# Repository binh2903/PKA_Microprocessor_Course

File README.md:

# PKA_Microprocessor_Course-
This repository contains the key submissions for the PKA Microprocessor Course, including classroom exercises, the mid-term report, and the final presentation.

Contents
Classroom Practice (1_THUC_HANH/)

This folder contains exercises and practical assignments completed during the course.

It includes hands-on work with microprocessors, programming tasks, and hardware-related experiments.

Mid-Term Report (2_Mid_Term_Report/)

A comprehensive report summarizing our progress and findings at the mid-point of the course.

It covers theoretical concepts, implementation details, and challenges encountered.

Final Presentation (3_Final_Presentation/)

The final presentation, showcasing our major project.

This includes an overview of the project's objectives, methodology, results, and conclusions.

This repository represents our team's collaborative efforts throughout the course, demonstrating both theoretical knowledge and practical application in microprocessor technology.

Note:
This README was generated with assistance from AI (ChatGPT) to ensure clarity and completeness.

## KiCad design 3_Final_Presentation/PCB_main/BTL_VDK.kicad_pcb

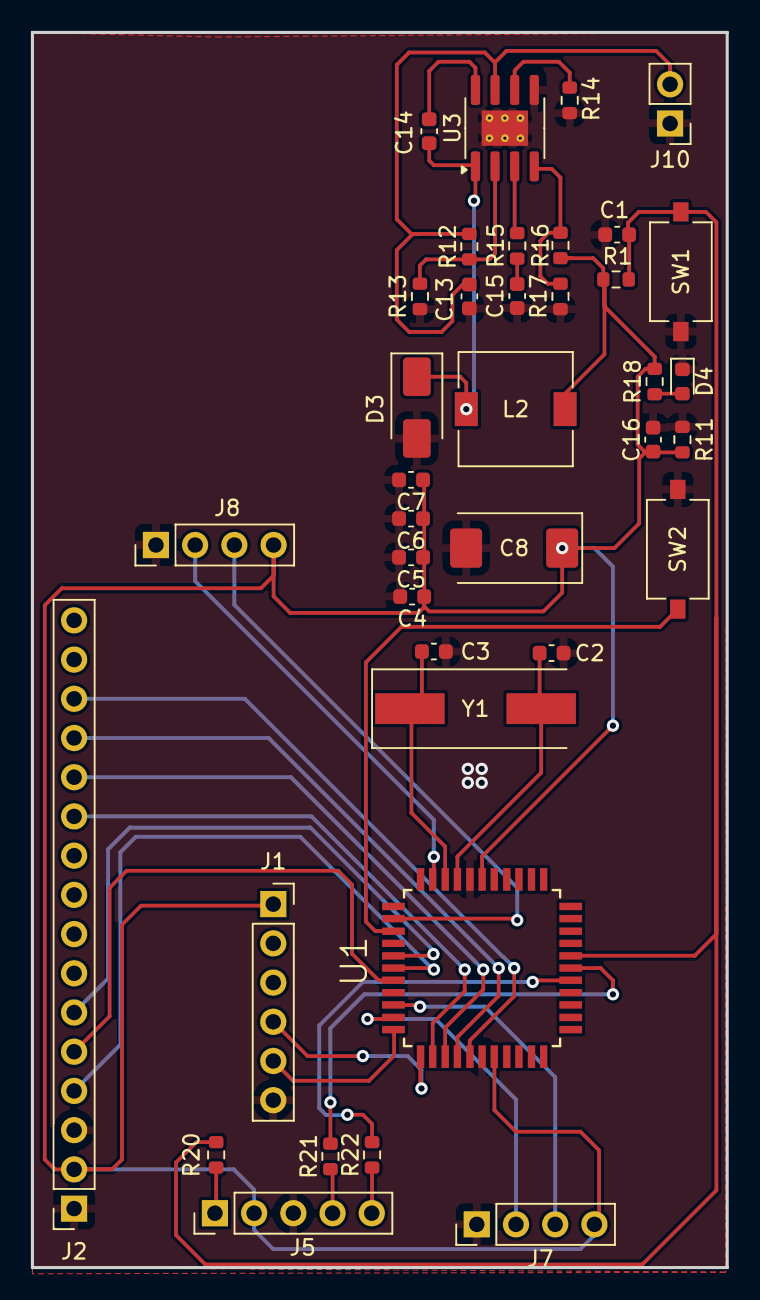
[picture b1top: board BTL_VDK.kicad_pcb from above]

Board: 2 copper layers, 45.0 x 80.0 mm, 38 parts (0 on the bottom side), 33 nets.

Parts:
C1, C5, C7: 10n; C_0603_1608Metric
C2, C3: 10p; C_0603_1608Metric
C4, C6, C13, C14: 100n; C_0603_1608Metric
C8: 47u; CP_EIA-7343-30_AVX-N
C15: 150p; C_0603_1608Metric
C16: 22u; C_0603_1608Metric
D3: SS34; D_SMA
D4: 5V; LED_0603_1608Metric
J1: Conn_01x06_Socket; PinSocket_1x06_P2.54mm_Vertical
J2: Conn_01x16_Socket; PinSocket_1x16_P2.54mm_Vertical
J5: ISP_CON; PinHeader_1x05_P2.54mm_Vertical
J7, J8: JST 2.54X4; PinHeader_1x04_P2.54mm_Vertical
J10: POWER; PinHeader_1x02_P2.54mm_Vertical
L2: 10uH; L_7.3x7.3_H3.5
R1, R11: 4.7K; R_0603_1608Metric
R12, R14, R15, R16, R17, R18: 10K; R_0603_1608Metric
R13: 10; R_0603_1608Metric
R20, R21, R22: 10R; R_0603_1608Metric
SW1: RST_BUT; SW_Tactile_SPST_NO_Straight_CK_PTS636Sx25SMTRLFS
SW2: RST_BUT_loadcell; SW_Tactile_SPST_NO_Straight_CK_PTS636Sx25SMTRLFS
U1: PIC16F887-I_PT; QFP80P1200X1200X120-44N
U3: MP1584EN-LF-P; SOIC-8-1EP_3.9x4.9mm_P1.27mm_EP2.29x3mm_ThermalVias
Y1: 20M; Crystal_SMD_HC49-SD

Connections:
12: C13.2, J10.2, R12.2, U3.7 (VIN)
+5V: C4.1, C5.1, C6.1, C7.1, C8.1, C16.2, J1.1, J2.2, J5.2, J7.4, J8.4, L2.2, R1.2, R11.2, R16.2, R18.2, U1.7 (VDD), U1.28 (VDD_2)
/MCU/D4: J2.11, U1.2 (RD4)
/MCU/D5: J2.12, U1.3 (RD5/P1B)
/MCU/D6: J2.13, U1.4 (RD6/P1C)
/MCU/D7: J2.14, U1.5 (RD7/P1D)
/MCU/DT: J8.2, U1.32 (RC0/T1OSO/T1CKI)
/MCU/E: J2.6, U1.38 (RD0)
/MCU/ECHO: J7.3, U1.42 (RC4/SDI/SDA)
/MCU/RS: J2.4, U1.39 (RD1)
/MCU/RW: J2.5, U1.40 (RD2)
/MCU/RX: J1.5, U1.44 (RC6/TX/CK)
/MCU/SCK: J8.3, U1.35 (RC1/T1OSCI/CCP2)
/MCU/TR: J7.2, U1.43 (RC5/SDO)
/MCU/TX: J1.4, U1.1 (RC7/RX/DT)
GND: C1.2, C2.2, C3.2, C4.2, C5.2, C6.2, C7.2, C8.2, C13.1, C15.1, C16.1, D3.2 (A), D4.1 (K), J1.6, J2.1, J2.3, J5.3, J7.1, J8.1, J10.1, R11.1, R13.1, R14.1, R17.1, SW1.1, SW2.2, U1.6 (VSS_2), U1.29 (VSS), U3.5 (GND), U3.9 (EPAD)
unnamed: C15.2, R15.1
unnamed: C14.2, D3.1 (K), L2.1, U3.1 (SW)
unnamed: D4.2 (A), R18.1
unnamed: J5.1, R20.2
unnamed: J5.4, R21.1
unnamed: J5.5, R22.1
unnamed: C3.1, U1.31 (RA6/OSC2/CLKOUT), Y1.1
unnamed: C2.1, U1.30 (RA7/OSC1/CLKIN), Y1.2
unnamed: R22.2, U1.16 (RB6/ICSPCLK)
unnamed: R21.2, U1.17 (RB7/ICSPDAT)
unnamed: SW2.1, U1.36 (RC2/P1A/CCP1)
unnamed: C14.1, U3.8 (BST)
unnamed: R15.2, U3.3 (COMP)
unnamed: R12.1, R13.2, U3.2 (EN)
unnamed: R16.1, R17.2, U3.4 (FB)
unnamed: R14.2, U3.6 (FREQ)
VPP: C1.1, R1.1, R20.1, SW1.2, U1.18 (RE3/~MCLR/VPP)

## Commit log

2025-03-30 Attach end-of-course report files
2025-03-31 Edit text
